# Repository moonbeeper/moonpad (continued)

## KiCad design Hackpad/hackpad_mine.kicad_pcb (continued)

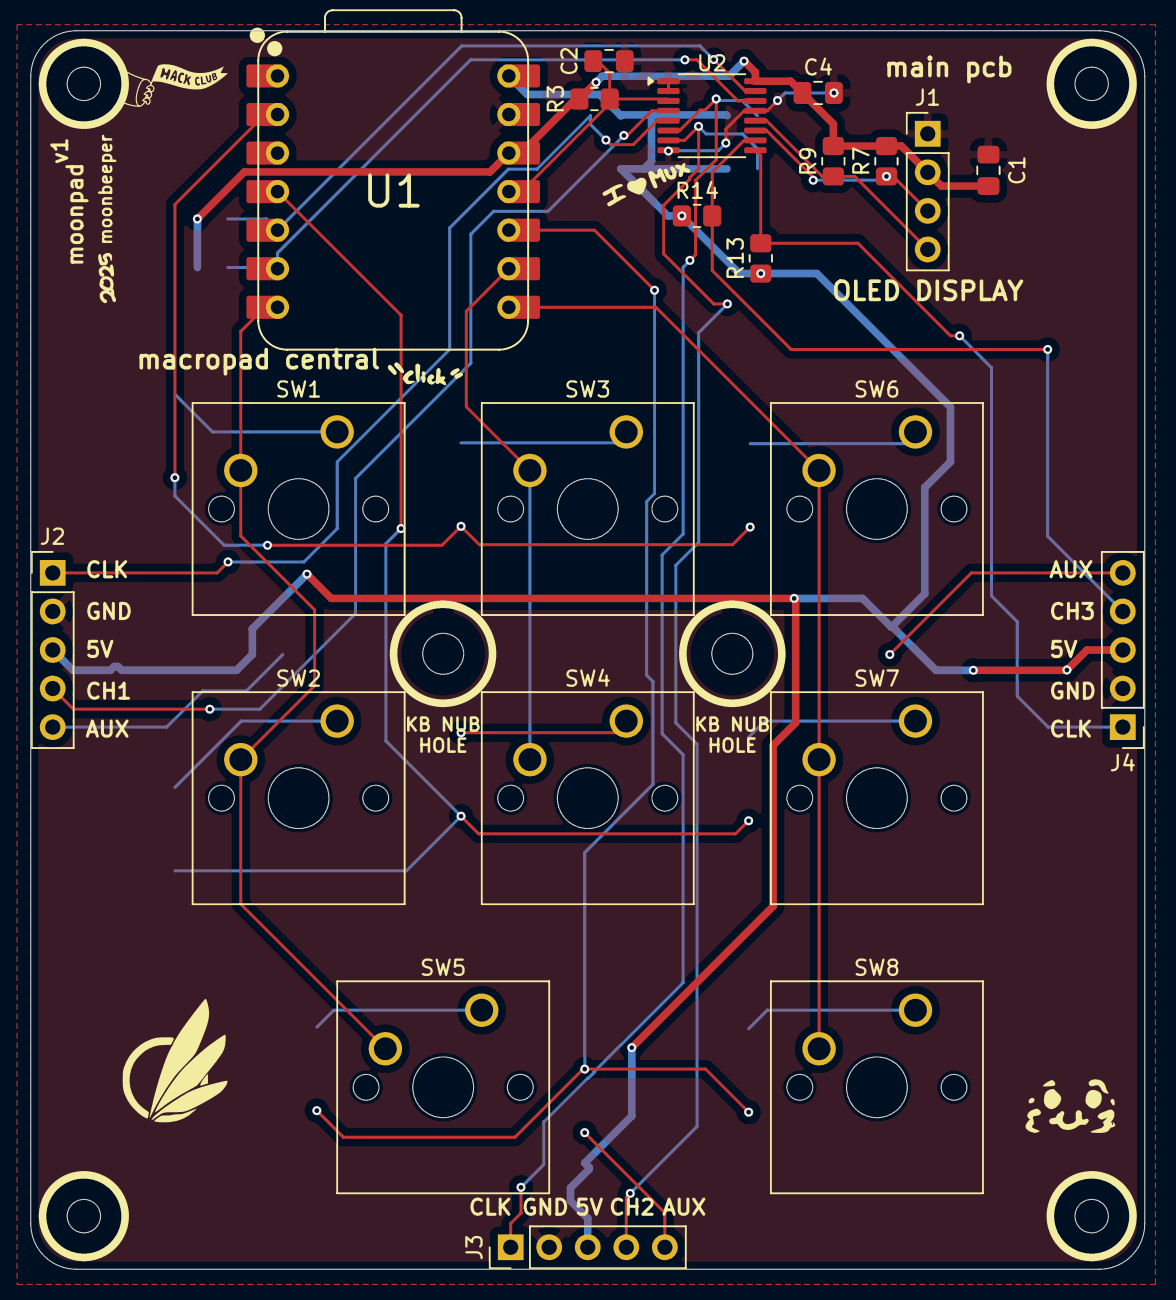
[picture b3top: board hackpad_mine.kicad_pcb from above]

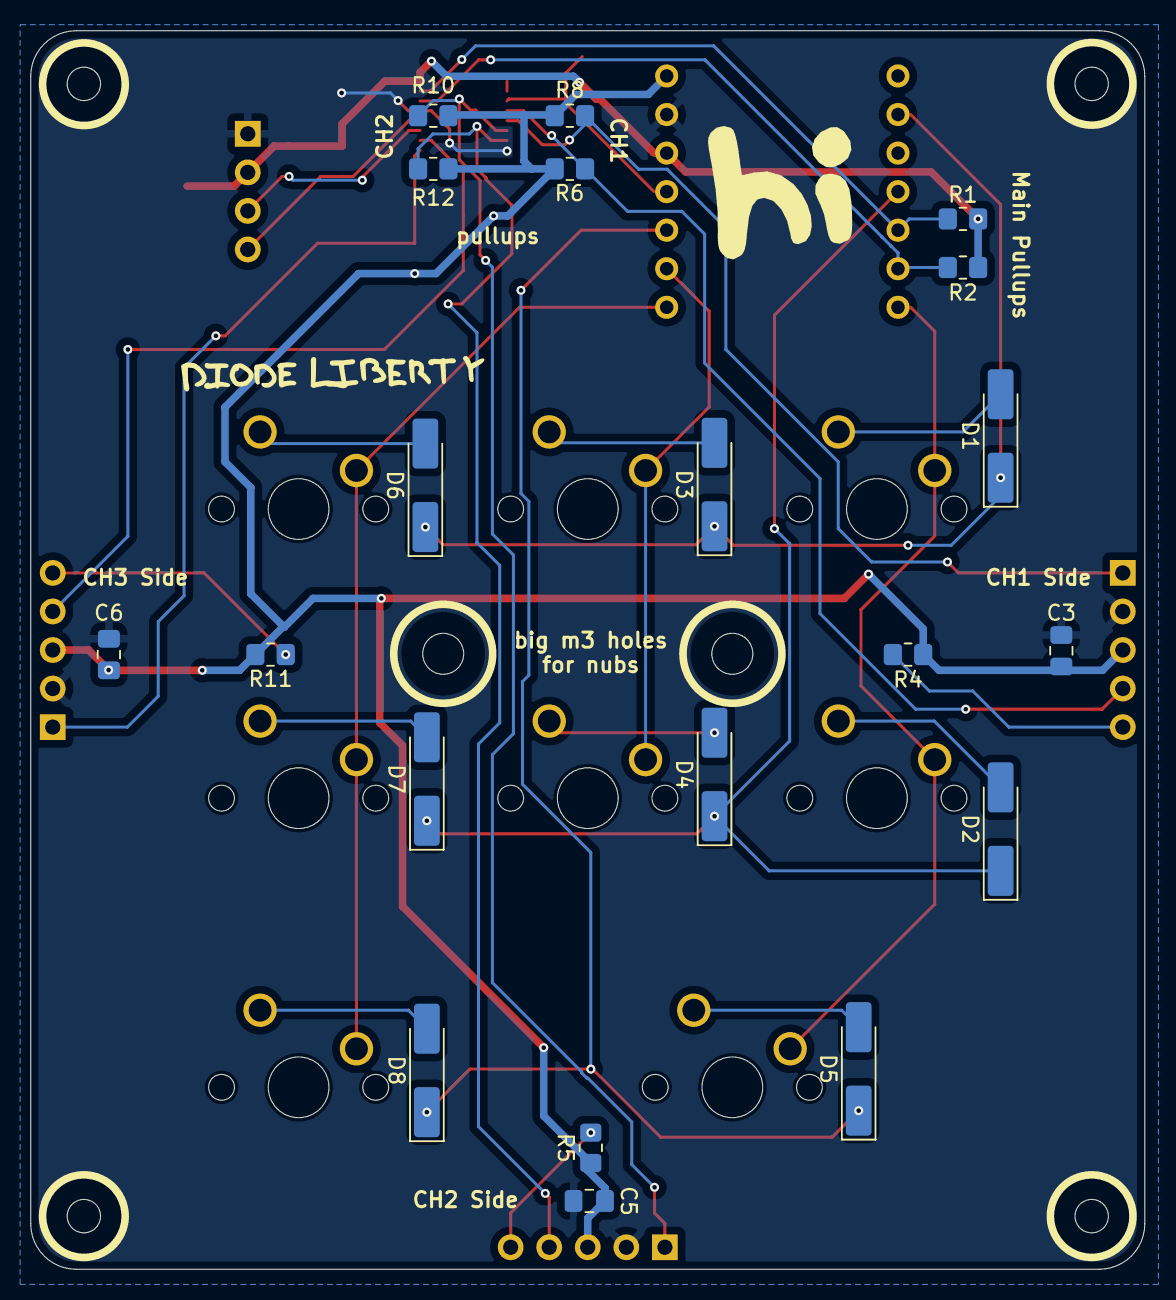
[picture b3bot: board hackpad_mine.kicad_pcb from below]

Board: 2 copper layers, 73.4 x 81.6 mm, 48 parts (20 on the bottom side), 31 nets.

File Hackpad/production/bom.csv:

Designator,Footprint,Quantity,Value,LCSC Part #
"C1, C2, C3, C4, C5, C6",0805,6,1uF,C116352
"D1, D2, D3, D4, D5, D6, D7, D8",D_MiniMELF_Handsoldering,8,1N4148,C68883
J1,PinHeader_1x04_P2.54mm_Vertical,1,Oled_128x32_Display,
J2,PinHeader_1x05_P2.54mm_Vertical,1,Right_Connector,
J3,PinHeader_1x05_P2.54mm_Vertical,1,Bottom_Connector,
J4,PinHeader_1x05_P2.54mm_Vertical,1,Left_Connector,
"R1, R10, R12, R13, R14, R2, R6, R7, R8, R9",0805,10,4.7k,C60816
"R11, R3, R4, R5",0805,4,10k,C17414
"SW1, SW2, SW3, SW4, SW5, SW6, SW7, SW8",SW_Cherry_MX_1.00u_PCB,8,SW_Push,
U1,XIAO-RP2040-DIP,1,XIAO-RP2040-DIP,
U2,TSSOP-16_4.4x5mm_P0.65mm,1,TCA9546APWR,C201653

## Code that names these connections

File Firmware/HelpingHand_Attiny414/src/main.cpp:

#include <Arduino.h>
#include <avr/sleep.h>

// These are the pin definitions for our helping hand.
#define ANALOG_SW_A0 8
#define ANALOG_SW_A1 9
#define MASTER_1 0
#define MASTER_2 1
#define MASTER_3 6
#define MASTER_4 3
#define SW_MUX_1 7
#define SW_MUX_2 10
#define SW_MUX_3 5
#define SW_MUX_4 4
#define MASTER_PMOS 2

// The master lines and sw mux lines are ordered in the same way as the master lines are defined.
const uint8_t MASTER_LINES[] = {MASTER_1, MASTER_2, MASTER_3, MASTER_4};
const uint8_t SW_MUX_LINES[] = {SW_MUX_1, SW_MUX_2, SW_MUX_3, SW_MUX_4};
const size_t NUM_MASTERS = sizeof(MASTER_LINES) / sizeof(MASTER_LINES[0]);

// put function declarations here:
void comsAnalogSwitch(uint8_t);
uint8_t waitForAnyMaster();
int8_t getMasterLine();

void setup()
{
  pinMode(ANALOG_SW_A0, OUTPUT);
  pinMode(ANALOG_SW_A1, OUTPUT);
  // using INPUT_PULLUP because I forgot to add a 10k ohm resistor to no leave dangling the pin.
  pinMode(MASTER_1, INPUT_PULLUP);
  pinMode(MASTER_2, INPUT_PULLUP);
  pinMode(MASTER_3, INPUT_PULLUP);
  pinMode(MASTER_4, INPUT_PULLUP);
  pinMode(SW_MUX_1, OUTPUT);
  pinMode(SW_MUX_2, OUTPUT);
  pinMode(SW_MUX_3, OUTPUT);
  pinMode(SW_MUX_4, OUTPUT);
  pinMode(MASTER_PMOS, OUTPUT);

  delay(10); // wait for the master lines to settle.

  // LOW -> Closed | HIGH -> Open
  // These are closed by default to avoid sending the coms back to its origin when not needed.
  digitalWrite(SW_MUX_1, LOW);
  digitalWrite(SW_MUX_2, LOW);
  digitalWrite(SW_MUX_3, LOW);
  digitalWrite(SW_MUX_4, LOW);

  uint8_t chosenLine = waitForAnyMaster();
  comsAnalogSwitch(chosenLine);

  // after choosing the master line we open the mux switches excluding the one we chose.
  for (uint8_t i = 0; i < NUM_MASTERS; i++)
  {
    if (i != chosenLine)
    {
      digitalWrite(SW_MUX_LINES[i], HIGH);
    }
    else
    {
      digitalWrite(SW_MUX_LINES[i], LOW); // just to be sure.
    }
  }
  delay(500); // wait for the attiny1616 to settle after the line selection. Might be a bit too much.

  // finally we open the PMOS switch
  digitalWrite(MASTER_PMOS, HIGH);
  // and we go to sleep for ever. zzz
  set_sleep_mode(SLEEP_MODE_PWR_DOWN);
  sleep_enable();
  sleep_cpu();
}

void loop()
{
  // put your main code here, to run repeatedly:
}

/// @brief Selects the I2C lines from the analog switch. This is used to select which master line is currently active.
/// @param channel
void comsAnalogSwitch(uint8_t channel)
{
  digitalWrite(ANALOG_SW_A0, channel & 0x01);
  digitalWrite(ANALOG_SW_A1, (channel >> 1) & 0x01);
}

/// @brief Loops until one of the master lines is HIGH. It's a blocking function.
/// @return The index of the master line that is HIGH
uint8_t waitForAnyMaster()
{
  while (true)
  {
    int chosenLine = getMasterLine();
    if (chosenLine >= 0)
    {
      return (uint8_t)chosenLine; // casting so I feel safe.
    }
    delay(10); // small delay between checks
  }
}

/// @brief Checks which master line is currently HIGH. If there are none, it returns -1.
/// If there's more than one, it returns the first one found.
/// @return The index of the master line
int8_t getMasterLine()
{
  for (uint8_t i = 0; i < NUM_MASTERS; i++)
  {
    if (digitalRead(MASTER_LINES[i]) == HIGH)
    {
      return i;
    }
  }

  return -1;
}

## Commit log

2025-07-13 second commit
2025-07-13 woops
2025-07-13 woops2
2025-07-13 trying to make github happy
2025-07-13 just uploading a tsv.
2025-07-19 updated pcb silkscreen for prettification
2025-07-19 bom out of stock modifications
2025-07-20 aliexpress experience
2025-07-28 update journal and readme
2026-05-16 first journal :)
2026-05-18 baby steps of macropad schematic
2026-05-20 forgot kicad project :)
2026-05-23 finished macropad schematic
2026-05-23 images in forge
2026-05-24 schematic cleanup
2026-05-25 journal: added the lcsc ids and mpns of the macropad components
2026-05-30 journal+pcb: lcsc ids, mpns, 3d models of components
